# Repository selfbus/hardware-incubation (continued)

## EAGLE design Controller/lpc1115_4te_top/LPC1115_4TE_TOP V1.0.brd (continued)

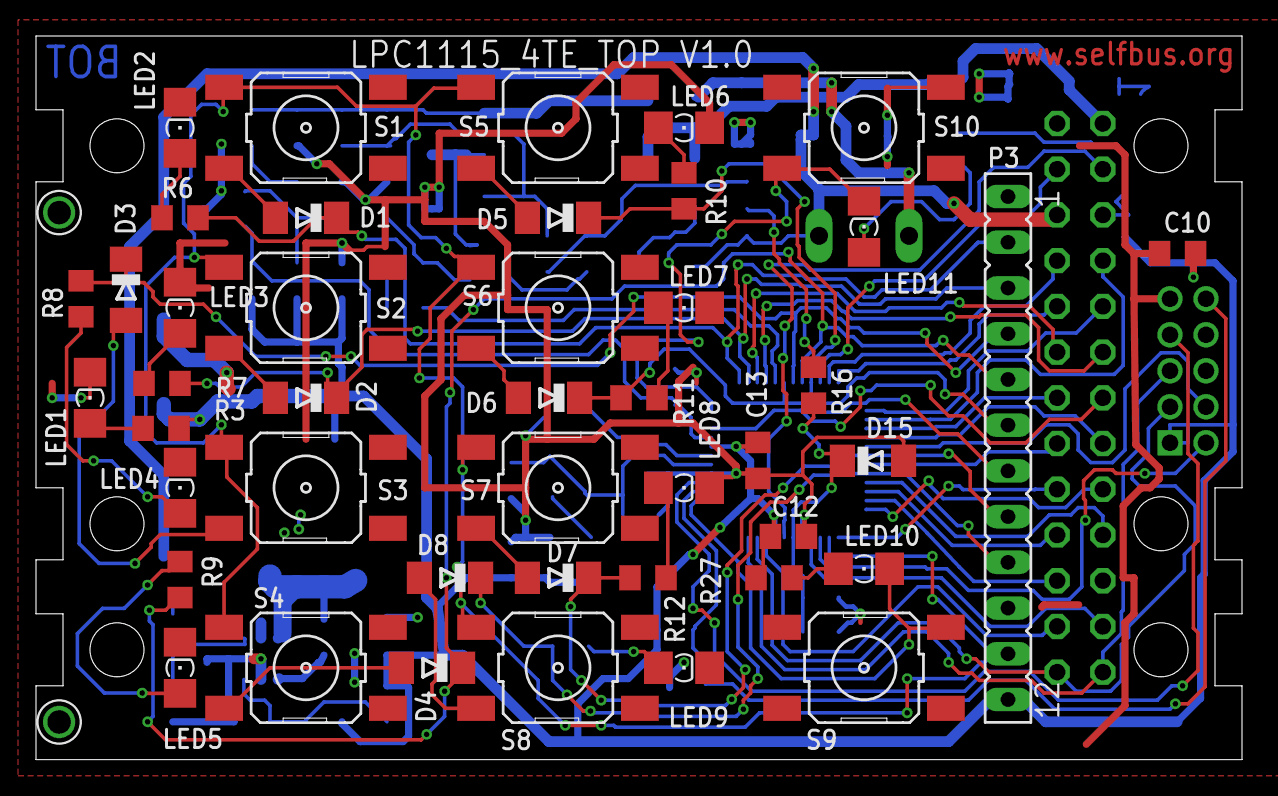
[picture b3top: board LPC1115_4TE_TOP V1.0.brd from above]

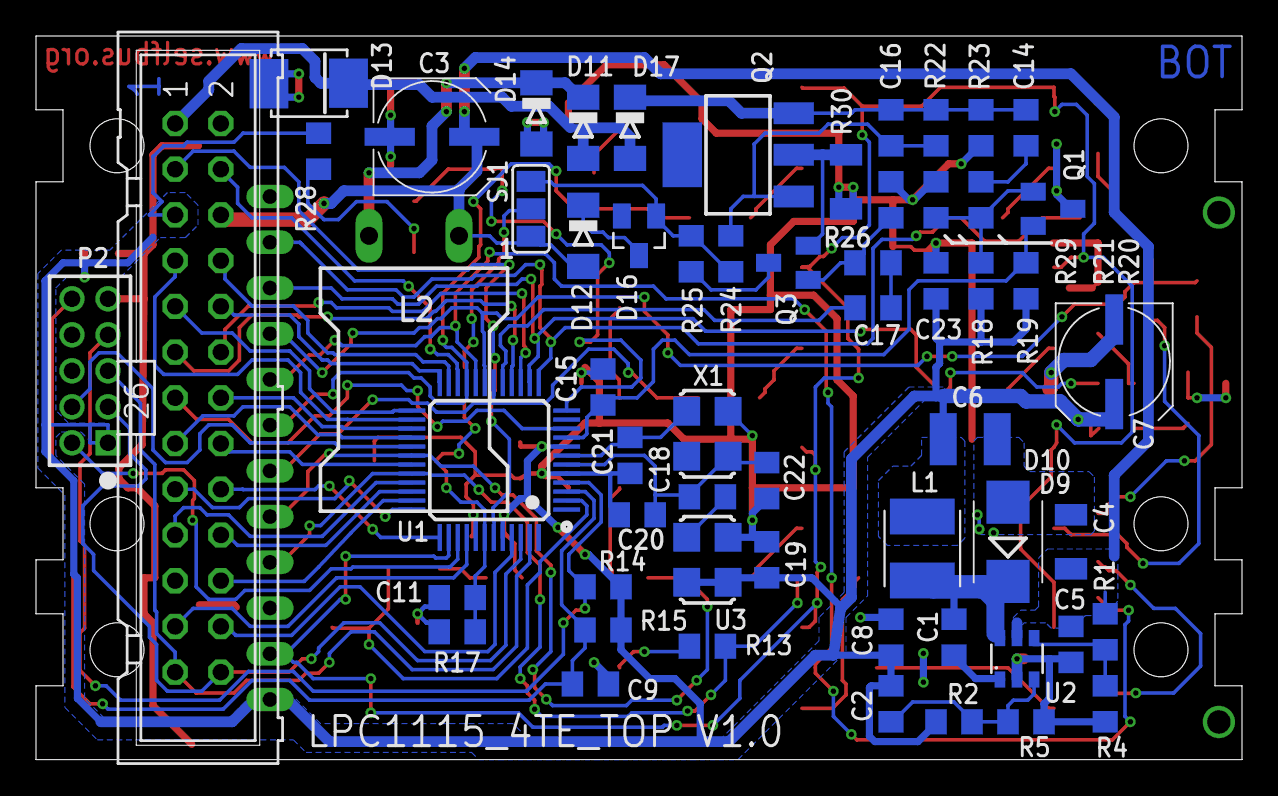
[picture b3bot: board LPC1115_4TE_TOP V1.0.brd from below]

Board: 2 copper layers, 67.0 x 40.2 mm, 106 parts (60 on the bottom side), 81 nets.

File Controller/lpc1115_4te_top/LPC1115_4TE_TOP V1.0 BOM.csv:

"Qty","Value","Package","Parts","Anmerkung","Lieferant","Bestellartikel","Artikelpreis","VPE","Postenpreis"
1,,"Platine LPC115_4TE_TOP",,,,,,,
1,,"ML26","P1",,"Reichelt","SL 2X13G 2,54","0,12",1,"0,12"
1,,"Pfostenbuchse 2x13pol 2,54mm",,,"Reichelt","PFL 26","0,19",1,"0,19"
1,"ISP","PINHD-2X05_2.00mm","P2",,"Reichelt","MPE 150-3-010","0,2",1,"0,2"
0,,"FE-1X12_2.54mm","P3","nur benötigt, wenn Bedienplatine aufgesteckt werden soll!","Reichelt","MPE 094-1-016","0,31",1,0
2,"18p","C-EUC0805M","C20, C21","wenn Quarz verwendet wird, vermutlich passen auch 15pF","TME","CC0805JRNPO9BN180","0,00973",1,"0,01946"
2,"100p","C-EUC0805M","C15, C18","C18: wenn Oszillator verwendet wird","Reichelt","NPO-G0805 100P","0,04",1,"0,08"
1,"220p","C-EUC0805M","C22","wenn Oszillator verwendet wird","Reichelt","NPO-G0805 220P","0,04",1,"0,04"
3,"10n","C-EUC0805M","C9, C16, C17"," ","Reichelt","X7R-G0805 10N","0,04",1,"0,12"
1,"10n(*)","C-EUC0805M","C11","Applikationsabhängig","Reichelt","X7R-G0805 10N","0,04",1,"0,04"
1,"15nF","C-EUC0805M","C1",,"Reichelt","X7R-G0805 15N","0,04",1,"0,04"
7,"100n","C-EUC0805M","C5, C8, C10, C12, C14, C19, C23",,"Reichelt","X7R-G0805 100N","0,04",1,"0,28"
1,"220n","C-EUC0805M","C2",,"Reichelt","X7R-G0805 0,22µ","0,04",1,"0,04"
1,"1µ/16V","C-EUC0805M","C13",,"Reichelt","X7R-G0805 1,0/16","0,04",1,"0,04"
1,"4.7µF/50V","C-EUC1206M","C4",,"Reichelt","X7R-G1206 4,7/50","0,23",1,"0,23"
1,"22µ/10V","C-EUC1210K","C6"," ","Reichelt","X7R-G1206 22/10","0,19",1,"0,19"
1,"FV 100/35 K-D8","CPOL-EUUD-6,3X7,7","C3",,"Reichelt","VF 100/35 K-D8","0,18",1,"0,18"
0,"100µ(*)","CPOL-EUUD-6,3X7,7","C7","abhängig vom Strombedarf der Applikation","Reichelt","VF 100/35 K-D8","0,18",1,0
1,"6.8µH","IND_FASTRON_1616FPSB","L1",,"Reichelt","L-1616FPS 6,8µ","0,3",1,"0,3"
1,"150mH","SD12BS11_LIEGEND","L2",,"Reichelt","L-11P 150M","0,55",1,"0,55"
1,"5R6","R-EU_R1206M","R30","RESISTOR, European symbol","Reichelt","SMD 1/4W 5,6","0,05",1,"0,05"
1,"680R","R-EU_R0805M","R5","RESISTOR, European symbol","Reichelt","SMD-0805 680","0,03",1,"0,03"
2,"1k","R-EU_R0805M","R22, R24","RESISTOR, European symbol","Reichelt","SMD-0805 1,00K","0,03",1,"0,06"
11,"1k5","R-EU_R0805M","R3, R6, R7, R8, R9, R10, R11, R12, R13, R27, R28","RESISTOR, European symbol","Reichelt","SMD-0805 1,50K","0,03",1,"0,33"
1,"2k2","R-EU_R0805M","R25","RESISTOR, European symbol","Reichelt","SMD-0805 2,20K","0,03",1,"0,03"
1,"2k4","R-EU_R0805M","R2","RESISTOR, European symbol","Reichelt","RND 0805 1 2,4K","0,02",1,"0,02"
1,"5k6","R-EU_R0805M","R26","RESISTOR, European symbol","Reichelt","SMD-0805 5,60K","0,03",1,"0,03"
2,"10k","R-EU_R0805M","R19, R20","RESISTOR, European symbol","Reichelt","SMD-0805 10,0K","0,03",1,"0,06"
1,"3k(*)","R-EU_R0805M","R17","RESISTOR, European symbol","Reichelt","RND 0805 1 3k0","0,02",1,"0,02"
1,"15k","R-EU_R0805M","R4","RESISTOR, European symbol","Reichelt","SMD-0805 15,0K","0,03",1,"0,03"
1,"47k","R-EU_R0805M","R21","RESISTOR, European symbol","Reichelt","SMD-0805 47,0K","0,03",1,"0,03"
1,"82k","R-EU_R0805M","R18","RESISTOR, European symbol","Reichelt","SMD-0805 82,0K","0,03",1,"0,03"
1,"36k(*)","R-EU_R0805M","R16","RESISTOR, European symbol","Reichelt","RND 0805 1 36k","0,02",1,"0,02"
4,"100k","R-EU_R0805M","R14, R15, R23, R29","RESISTOR, European symbol","Reichelt","SMD-0805 100K","0,03",1,"0,12"
1,"390k","R-EU_R0805M","R1","RESISTOR, European symbol","Reichelt","SMD-0805 390K","0,03",1,"0,03"
0,"SMAJ40CA","D-SMB","D13","nur wenn auf der Applikationsplatine keine vorhanden ist","Oldis Shop","SMAJ 40 AC Überspannungsdiode","0,2",1,0
12,"TS4148","DIODE-MINIMELF","D1, D2, D3, D4, D5, D6, D7, D8, D11, D12, D14, D17"," ","Reichelt","TS 4148-1206","0,04",1,"0,48"
0,"RB060M-60(*)","DIODE-SOD123","D9","nicht bestückt, es wird D10 verwendet",,,0,0,0
1,"STPS1L60A","DIODE-SMB","D10"," ","TME","STPS1L60A","0,089",1,"0,089"
0,"(*)","DIODE-MINIMELF","D15","Zenerdiode applikationsabhängig","Reichelt","SMD ZF 3,6","0,04",1,0
1,"7V5","ZENER-DIODESOT23","D16",,"Reichelt","SMD ZD 7,5","0,04",1,"0,04"
8,"grün","LEDSMT1206","LED2, LED3, LED4, LED5, LED6, LED7, LED8, LED9","extra helle LEDs, benötigen daher nur wenig Strom","Reichelt","LED EL 1206 GR2","0,12",1,"0,96"
2,"red","LEDSMT1206","LED1, LED10, LED11","üblicherweise wird nur eine der LEDs LED10, LED11 bestückt","Reichelt","LED EL 1206 RT","0,1",1,"0,2"
1,"BC856","BC856BSMD","Q1",,"Reichelt","BC 856B SMD","0,04",1,"0,04"
1,"BCP52","SOT223","Q2",,"Reichelt","BCP 52-16 SMD","0,14",1,"0,14"
1,"BC847C","BC847","Q3 (in V1.0 bedruckt mit T1)",,"Reichelt","BC 847C SMD","0,04",1,"0,04"
0,,"10-XXSMD","S1, S2, S3, S4, S5, S6, S7, S8","Benötigte Länge des Tasters abhängig von Applikation! (7mm ist Minimum, eher 8)","Reichelt","TASTER 9316","0,23",1,0
8,,"10-XXSMD","S1, S2, S3, S4, S5, S6, S7, S8","Taster 9318 8mm (Länge für out6-cs, jedoch nur 6 Stück notwendig)","Reichelt","TASTER 9318","0,21",1,"1,68"
1,"Prog","10-XXSMD","S9, S10","üblicherweise wird nur einer der beiden Taster bestückt","Reichelt","TASTER 9315","0,15",1,"0,15"
1,"LPC1115FBD48","LPC1113/4/5_QFP48_XLSERIES","U1","LPC1115FBD48 (auch bei TME zu bekommen)","Oldis Shop","NXP LPC1115","2,5",1,"2,5"
1,"BD9G101","BD9G101G-SOT23-6","U2","Schaltregler","Oldis Shop","Schaltregler BD9G101G-CT-ND","1,5",1,"1,5"
1,"XO32 12MHz","ASFL","U3","CRYSTAL CLOCK OSCILLATORS","Reichelt","XO32 12,00000","1,3",1,"1,3"
0,"12MHz","CRYSTALASF","X1","Quarz alternativ zum Oszillator! Der Reichelt-Typ hat 12pF statt 10pF Nenn","Reichelt","12,000000-MT","0,95",1,0
10,,,,"Lichtleiter 4,7mm (für out6-cs nur 8 Stück notwendig)","Conrad",183133,"0,65",1,"6,5"

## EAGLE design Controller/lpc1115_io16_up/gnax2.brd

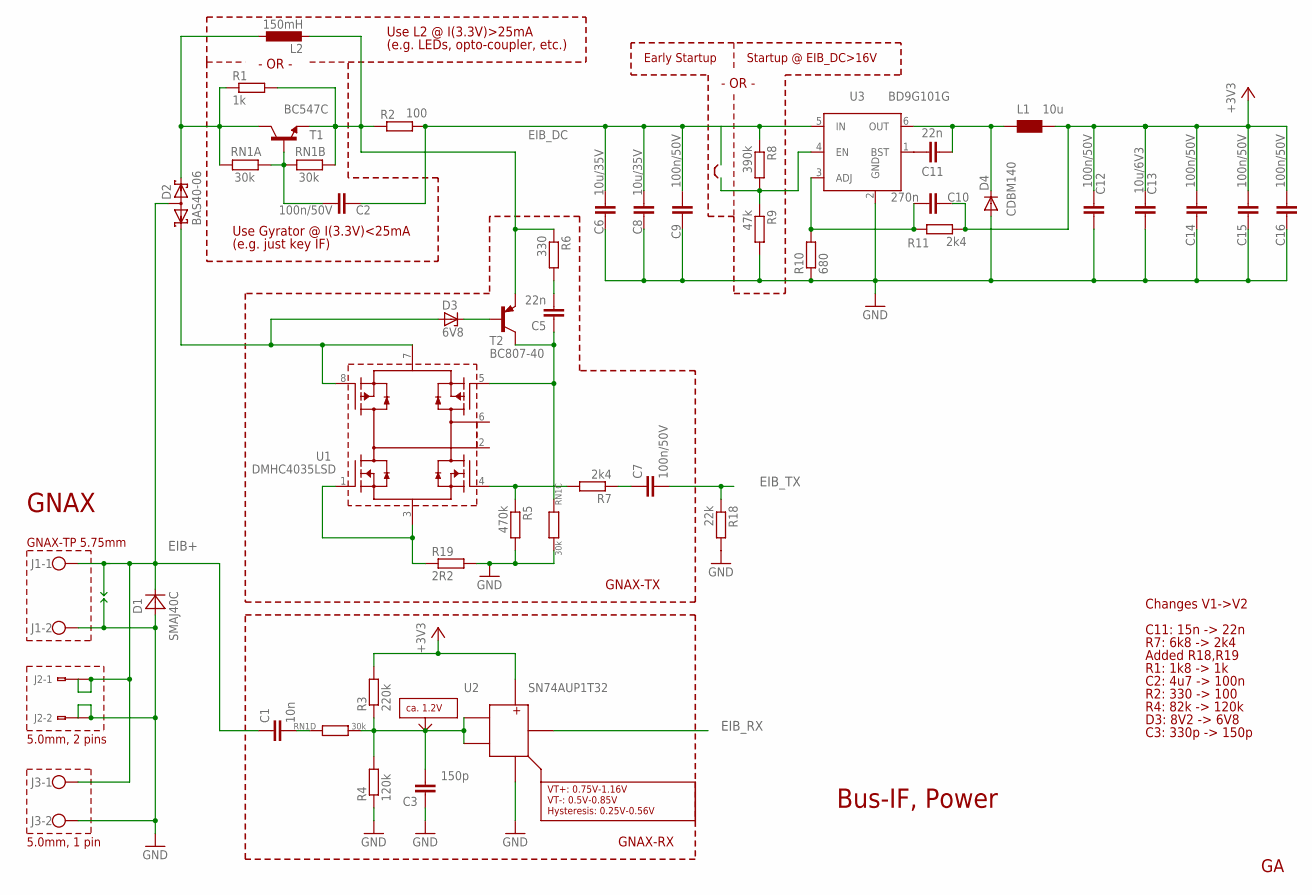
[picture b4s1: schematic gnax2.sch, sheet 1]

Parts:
C1: 10n; C0603K
C2, C7, C9, C12, C14, C15, C16: 100n/50V; C0603K
C3: 150p; C0603K
C5, C11: 22n; C0603K
C6, C8: 10u/35V; C1206K
C10: 270n; C0603K
C13: 10u/6V3; C0603K
D1: SMAJ40C; SMA
D2: BAS40-06; SOT23
D3: 6V8; SOT23
D4: CDBM140; SOD123
J1: CON_2KNX; KNX2
J2-1, J2-2: 236-740-5,08; 236-4XX
J3: CON_2; W237-102
L1: 10u; L_ELL3
L2: 150mH; 0204/5
R1: 1k; R0603
R2: 100; R0603
R3: 220k; R0603
R4: 120k; R0603
R5: 470k; R0603
R6: 330; R0603
R7, R11: 2k4; R0603
R8: 390k; R0603
R9: 47k; R0603
R10: 680; R0603
R18: 22k; R0603
R19: 2R2; R0805
RN1: 30k; 1206_8
T1: BC547C; SOT23
T2: BC807-40; SOT23-BEC
U1: DMHC4035LSD; SOP8
U2: SN74AUP1T32; SC88A
U3: BD9G101G; SOT23-6

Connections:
EIB+: C1.1, D1.C, D2.3 (AA), J1.1, J2-1.1@1 (A1), J2-1.1@2 (B1), J3.1; also elsewhere on the board
EIB_DC: C2.1, C6.1, C8.1, C9.2, R2.2, R8.1, U3.5 (IN); also elsewhere on the board
EIB_RX: U2.4 (Y); also elsewhere on the board
EIB_TX: C7.2, R18.1; also elsewhere on the board
FX: R19.1, U1.1 (N1G), U1.3 (N1S/N2S)
GND: C3.1, C6.2, C8.2, C9.1, C12.1, C13.1, C14.1, C15.1, C16.1, D1.A, D4.A, J1.2, J2-2.1@2 (B1), J3.2, R4.1, R5.2, R9.2, R10.1, R18.2, R19.2, RN1.6, U2.3 (GND), U3.2 (GND); also elsewhere on the board
LX: C11.1, D4.C, L1.P$1, U3.6 (OUT)
unnamed: D2.1 (K1), D3.1 (A), U1.7 (P1S/P2S), U1.8 (P1G)
unnamed: C1.2, RN1.4
unnamed: R5.1, R7.2, U1.4 (N2G)
unnamed: C7.1, R7.1
unnamed: D2.2 (K2), L2.1, R1.1, RN1.1, T1.3 (C)
unnamed: C5.1, RN1.3, T2.C, U1.5 (P2G)
unnamed 43: C3.2, R3.1, R4.2, RN1.5, U2.1 (A), U2.2 (B); also elsewhere on the board
unnamed: C5.2, R6.2
unnamed: C11.2, U3.1 (BST)
unnamed: R8.2, R9.1, U3.4 (EN)
unnamed: C10.1, R10.2, R11.1, U3.3 (ADJ)
unnamed: C2.2, RN1.7, RN1.8, T1.1 (B)
unnamed: D3.3 (C), T2.B
unnamed: L2.2, R1.2, R2.1, R6.1, RN1.2, T1.2 (E), T2.E
VCC: C10.2, C12.2, C13.2, C14.2, C15.2, C16.2, L1.P$2, R3.2, R11.2, U2.5 (VCC); also elsewhere on the board

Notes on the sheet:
Startup @ EIB_DC>16V
Bus-IF, Power
GNAX
GNAX-TX
GNAX-RX
ca. 1.2V
5.0mm, 1 pin
GNAX-TP 5.75mm
Use Gyrator @ I(3.3V)<25mA
C11: 15n -> 22n
R7: 6k8 -> 2k4
Added R18,R19
R1: 1k8 -> 1k
C2: 4u7 -> 100n
R2: 330 -> 100
R4: 82k -> 120k
Changes V1->V2
VT+: 0.75V-1.16V VT-: 0.5V-0.85V Hysteresis: 0.25V-0.56V
Early Startup
Use L2 @ I(3.3V)>25mA
- OR -
5.0mm, 2 pins
(e.g. just key IF)
(e.g. LEDs, opto-coupler, etc.)
D3: 8V2 -> 6V8
C3: 330p -> 150p

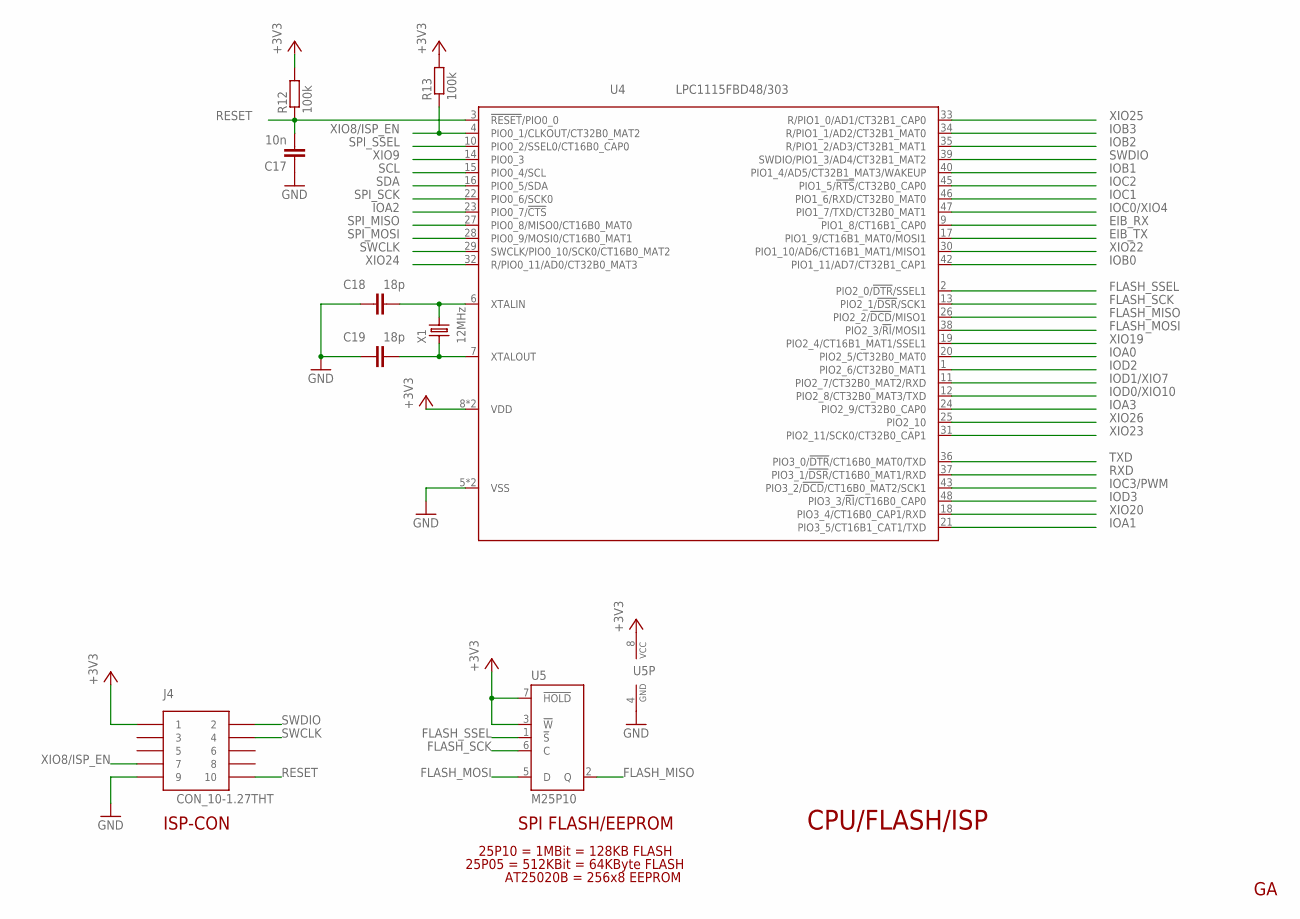
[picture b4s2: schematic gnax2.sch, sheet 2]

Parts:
C17: 10n; C0603K
C18, C19: 18p; C0603K
J4: CON_10-1.27THT; CON2X5_127-THT
R12, R13: 100k; R0603
U4: LPC1115FBD48/303; SOT313-2
U5: M25P10; SO08
X1: 12MHz; XTAL_5X3.2

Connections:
EIB_RX: U4.9 (PIO1_8/CT16B1_CAP0); also elsewhere on the board
EIB_TX: U4.17 (PIO1_9/CT16B1_MAT0/MOSI1); also elsewhere on the board
FLASH_MISO: U4.26 (PIO2_2/!DCD!/MISO1), U5.2 (Q)
FLASH_MOSI: U4.38 (PIO2_3/!RI!/MOSI1), U5.5 (D)
FLASH_SCK: U4.13 (PIO2_1/!DSR!/SCK1), U5.6 (C)
FLASH_SSEL: U4.2 (PIO2_0/!DTR!/SSEL1), U5.1 (!S)
GND: C17.1, C18.1, C19.1, J4.9, U4.5 (VSS), U4.41 (VSS), U5.4 (GND); also elsewhere on the board
IOA0: U4.20 (PIO2_5/CT32B0_MAT0); also elsewhere on the board
IOA1: U4.21 (PIO3_5/CT16B1_CAT1/TXD); also elsewhere on the board
IOA2: U4.23 (PIO0_7/!CTS!); also elsewhere on the board
IOA3: U4.24 (PIO2_9/CT32B0_CAP0); also elsewhere on the board
IOB0: U4.42 (PIO1_11/AD7/CT32B1_CAP1); also elsewhere on the board
IOB1: U4.40 (PIO1_4/AD5/CT32B1_MAT3/WAKEUP); also elsewhere on the board
IOB2: U4.35 (R/PIO1_2/AD3/CT32B1_MAT1); also elsewhere on the board
IOB3: U4.34 (R/PIO1_1/AD2/CT32B1_MAT0); also elsewhere on the board
IOC0/XIO4: U4.47 (PIO1_7/TXD/CT32B0_MAT1); also elsewhere on the board
IOC1: U4.46 (PIO1_6/RXD/CT32B0_MAT0); also elsewhere on the board
IOC2: U4.45 (PIO1_5/!RTS!/CT32B0_CAP0); also elsewhere on the board
IOC3/PWM: U4.43 (PIO3_2/!DCD!/CT16B0_MAT2/SCK1); also elsewhere on the board
IOD0/XIO10: U4.12 (PIO2_8/CT32B0_MAT3/TXD); also elsewhere on the board
IOD1/XIO7: U4.11 (PIO2_7/CT32B0_MAT2/RXD); also elsewhere on the board
IOD2: U4.1 (PIO2_6/CT32B0_MAT1); also elsewhere on the board
IOD3: U4.48 (PIO3_3/!RI!/CT16B0_CAP0); also elsewhere on the board
unnamed: C19.2, U4.7 (XTALOUT), X1.1
unnamed: C18.2, U4.6 (XTALIN), X1.2
RESET: C17.2, J4.10, R12.1, U4.3 (!RESET!/PIO0_0)
RXD: U4.37 (PIO3_1/!DSR!/CT16B0_MAT1/RXD); also elsewhere on the board
SCL: U4.15 (PIO0_4/SCL); also elsewhere on the board
SDA: U4.16 (PIO0_5/SDA); also elsewhere on the board
SPI_MISO: U4.27 (PIO0_8/MISO0/CT16B0_MAT0); also elsewhere on the board
SPI_MOSI: U4.28 (PIO0_9/MOSI0/CT16B0_MAT1); also elsewhere on the board
SPI_SCK: U4.22 (PIO0_6/SCK0); also elsewhere on the board
SPI_SSEL: U4.10 (PIO0_2/SSEL0/CT16B0_CAP0); also elsewhere on the board
SWCLK: J4.4, U4.29 (SWCLK/PIO0_10/SCK0/CT16B0_MAT2)
SWDIO: J4.2, U4.39 (SWDIO/PIO1_3/AD4/CT32B1_MAT2)
TXD: U4.36 (PIO3_0/!DTR!/CT16B0_MAT0/TXD); also elsewhere on the board
VCC: J4.1, R12.2, R13.2, U4.8 (VDD), U4.44 (VDD), U5.3 (!W), U5.7 (!HOLD), U5.8 (VCC); also elsewhere on the board
XIO8/ISP_EN: J4.7, R13.1, U4.4 (PIO0_1/CLKOUT/CT32B0_MAT2); also elsewhere on the board
XIO9: U4.14 (PIO0_3); also elsewhere on the board
XIO19: U4.19 (PIO2_4/CT16B1_MAT1/SSEL1); also elsewhere on the board
XIO20: U4.18 (PIO3_4/CT16B0_CAP1/RXD); also elsewhere on the board
XIO22: U4.30 (PIO1_10/AD6/CT16B1_MAT1/MISO1); also elsewhere on the board
XIO23: U4.31 (PIO2_11/SCK0/CT32B0_CAP1); also elsewhere on the board
XIO24: U4.32 (R/PIO0_11/AD0/CT32B0_MAT3); also elsewhere on the board
XIO25: U4.33 (R/PIO1_0/AD1/CT32B1_CAP0); also elsewhere on the board
XIO26: U4.25 (PIO2_10); also elsewhere on the board

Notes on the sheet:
CPU/FLASH/ISP
ISP-CON
SPI FLASH/EEPROM
25P10 = 1MBit = 128KB FLASH
25P05 = 512KBit = 64KByte FLASH
AT25020B = 256x8 EEPROM

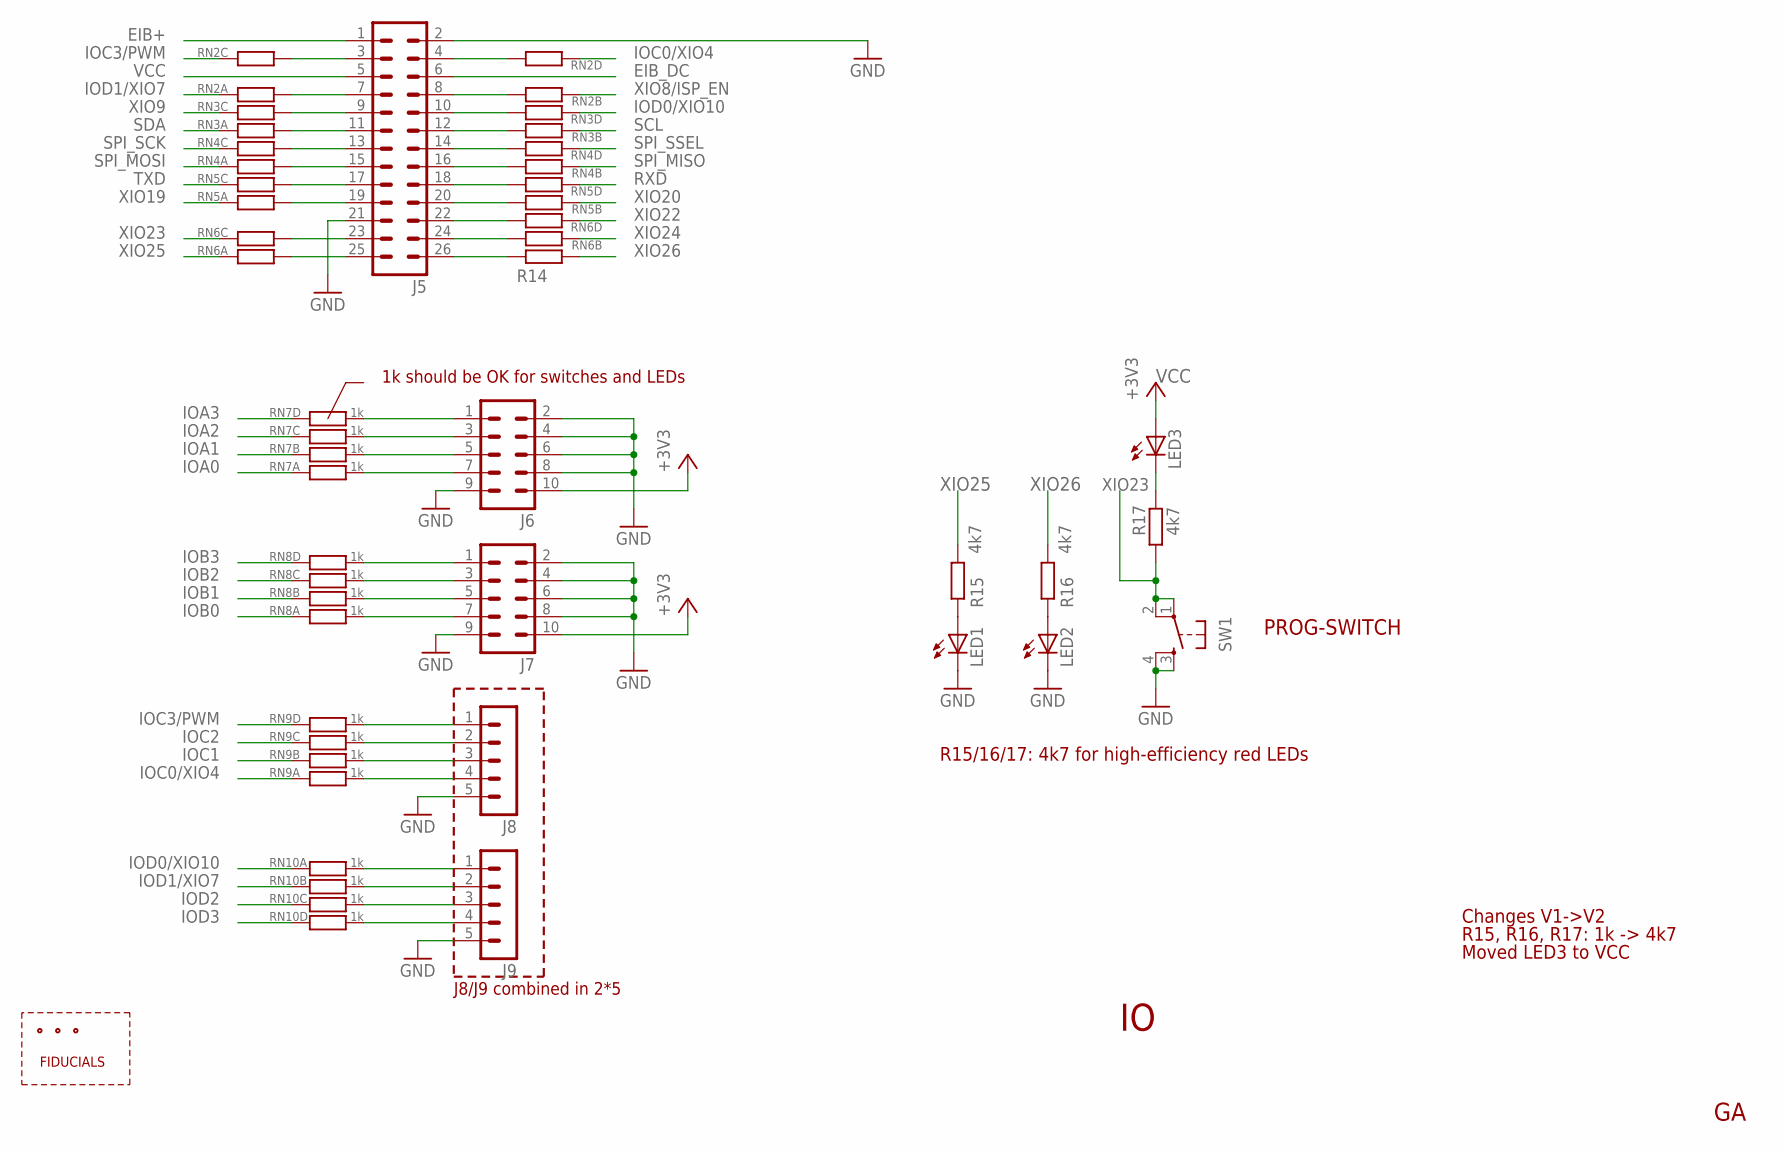
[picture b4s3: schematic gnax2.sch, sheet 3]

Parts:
J5: MA13-2
J6, J7: MA05-2
J8, J9: MA05-1
LED1, LED2, LED3: LEDCHIP-LED0805; CHIP-LED0805
R14: R-EU_R0603; R0603
R15, R16, R17: 4k7; R0603
RN2, RN3, RN4, RN5, RN6: RNET12061; 1206_8
RN7, RN8, RN9, RN10: 1k; 1206_8
SW1: SWITCH_X; SWITCH_PTS810
X3, X8, X9: FIDUCIAL_0.6-1.2MM; FIDUCIAL0.6-1.2

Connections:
EIB+: J5.1; also elsewhere on the board
EIB_DC: J5.6; also elsewhere on the board
GND: J5.2, J5.21, J6.2, J6.4, J6.6, J6.8, J6.9, J7.2, J7.4, J7.6, J7.8, J7.9, J8.5, J9.5, LED1.C, LED2.C, SW1.3 (S), SW1.4 (S1); also elsewhere on the board
IOA0: RN7.1; also elsewhere on the board
IOA1: RN7.2; also elsewhere on the board
IOA2: RN7.3; also elsewhere on the board
IOA3: RN7.4; also elsewhere on the board
IOB0: RN8.1; also elsewhere on the board
IOB1: RN8.2; also elsewhere on the board
IOB2: RN8.3; also elsewhere on the board
IOB3: RN8.4; also elsewhere on the board
IOC0/XIO4: RN2.4, RN9.1; also elsewhere on the board
IOC1: RN9.2; also elsewhere on the board
IOC2: RN9.3; also elsewhere on the board
IOC3/PWM: RN2.3, RN9.4; also elsewhere on the board
IOD0/XIO10: RN3.4, RN10.1; also elsewhere on the board
IOD1/XIO7: RN2.1, RN10.2; also elsewhere on the board
IOD2: RN10.3; also elsewhere on the board
IOD3: RN10.4; also elsewhere on the board
unnamed: J6.7, RN7.8
unnamed: LED1.A, R15.1
unnamed: J6.5, RN7.7
unnamed: J6.3, RN7.6
unnamed: J6.1, RN7.5
unnamed: J7.5, RN8.7
unnamed: J7.3, RN8.6
unnamed: J7.7, RN8.8
unnamed: J7.1, RN8.5
unnamed: LED3.C, R17.2
unnamed: J8.3, RN9.7
unnamed: J8.2, RN9.6
unnamed: J8.4, RN9.8
unnamed: J9.1, RN10.8
unnamed: J9.2, RN10.7
unnamed: J9.3, RN10.6
unnamed: J9.4, RN10.5
unnamed: J8.1, RN9.5
unnamed: LED2.A, R16.1
unnamed: J5.3, RN2.6
unnamed: J5.7, RN2.8
unnamed: J5.9, RN3.6
unnamed: J5.11, RN3.8
unnamed: J5.13, RN4.6
unnamed: J5.4, RN2.5
unnamed: J5.8, RN2.7
unnamed: J5.10, RN3.5
unnamed: J5.12, RN3.7
unnamed: J5.14, RN4.5
unnamed: J5.15, RN4.8
unnamed: J5.17, RN5.6
unnamed: J5.16, RN4.7
unnamed: J5.18, RN5.5
unnamed: J5.19, RN5.8
unnamed: J5.20, RN5.7
unnamed: J5.22, RN6.5
unnamed: J5.23, RN6.6
unnamed: J5.24, RN6.7
unnamed: J5.25, RN6.8
unnamed: J5.26, R14.1
RXD: RN5.4; also elsewhere on the board
SCL: RN3.2; also elsewhere on the board
SDA: RN3.1; also elsewhere on the board
SPI_MISO: RN4.2; also elsewhere on the board
SPI_MOSI: RN4.1; also elsewhere on the board
SPI_SCK: RN4.3; also elsewhere on the board
SPI_SSEL: RN4.4; also elsewhere on the board
TXD: RN5.3; also elsewhere on the board
VCC: J5.5, J6.10, J7.10, LED3.A; also elsewhere on the board
XIO8/ISP_EN: RN2.2; also elsewhere on the board
XIO9: RN3.3; also elsewhere on the board
XIO19: RN5.1; also elsewhere on the board
XIO20: RN5.2; also elsewhere on the board
XIO22: RN6.4; also elsewhere on the board
XIO23: R17.1, RN6.3, SW1.1, SW1.2 (P1); also elsewhere on the board
XIO24: RN6.2; also elsewhere on the board
XIO25: R15.2, RN6.1; also elsewhere on the board
XIO26: R14.2, R16.2; also elsewhere on the board

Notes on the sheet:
FIDUCIALS
1k should be OK for switches and LEDs
R15, R16, R17: 1k -> 4k7
Changes V1->V2
R15/16/17: 4k7 for high-efficiency red LEDs
J8/J9 combined in 2*5
PROG-SWITCH
Moved LED3 to VCC

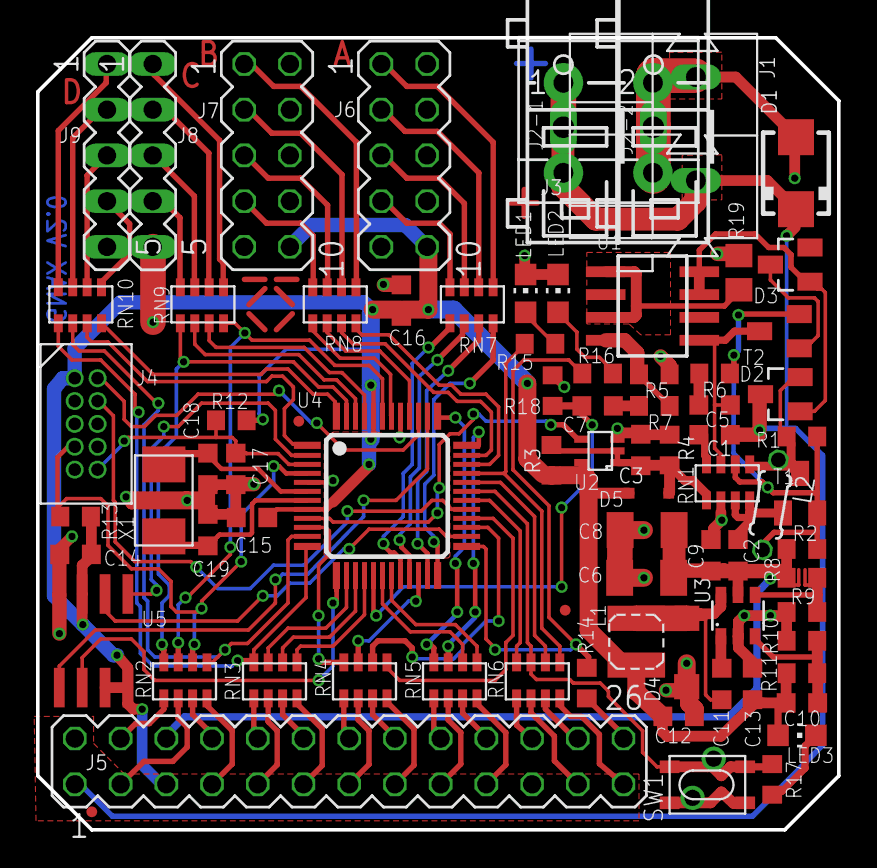
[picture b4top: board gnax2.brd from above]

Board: 4 copper layers, 44.5 x 44.0 mm, 80 parts (0 on the bottom side), 104 nets.

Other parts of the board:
D5: 1N4148WX-TP; SOD323-R
U$1: BAYCOM_LOGO

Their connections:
unnamed 43: D5.A; also elsewhere on the board
VCC: D5.C; also elsewhere on the board
